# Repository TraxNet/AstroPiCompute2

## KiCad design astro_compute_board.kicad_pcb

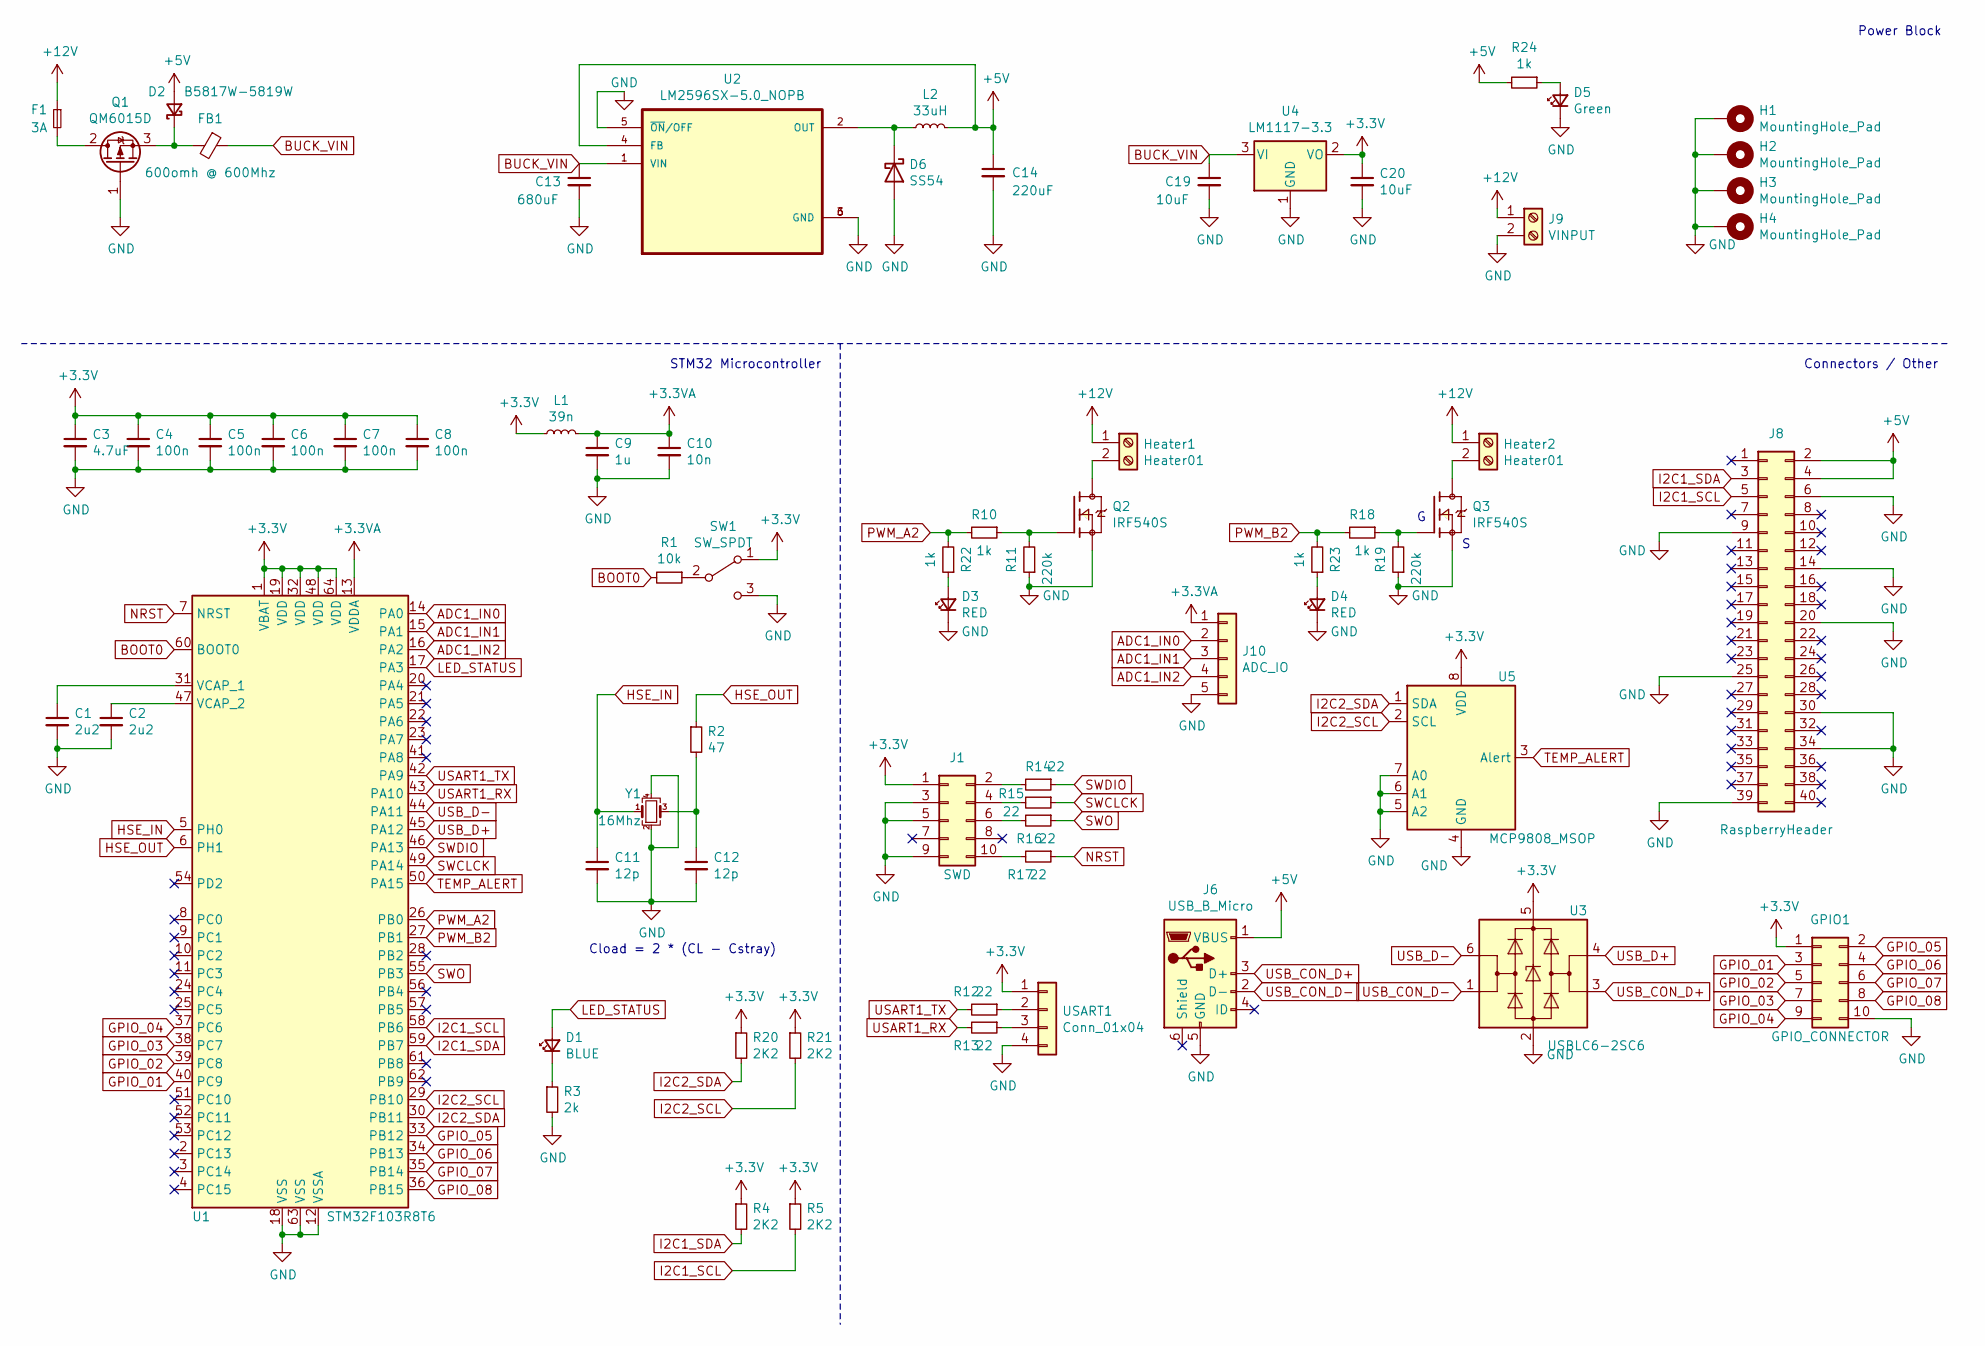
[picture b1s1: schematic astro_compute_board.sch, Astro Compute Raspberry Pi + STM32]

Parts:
C1, C2: 2u2; C_0603_1608Metric; LCSC Part # C23630
C3: 4.7uF; C_0402_1005Metric; LCSC Part # C23733
C4, C5, C6, C7, C8: 100n; C_0402_1005Metric; LCSC Part # C1525
C9: 1u; C_0402_1005Metric; LCSC Part # C52923
C10: 10n; C_0402_1005Metric; LCSC Part # C15195
C11, C12: 12p; C_0402_1005Metric; LCSC Part # C1547
C13: 680uF; CP_Radial_D8.0mm_P3.50mm; LCSC Part # C13585
C14: 220uF; CP_Radial_D6.3mm_P2.50mm; LCSC Part # C13585
C19, C20: 10uF; C_1206_3216Metric; LCSC Part # C13585
D1: BLUE; LED_0603_1608Metric; LCSC Part # C72041
D2: B5817W-5819W; D_SOD-123; LCSC Part # C8598
D3, D4: RED; LED_0603_1608Metric; LCSC Part # C2286
D5: Green; LED_0603_1608Metric; LCSC Part # C72043
D6: SS54; D_SMA; LCSC Part # C22452
F1: 3A; Fuse_1206_3216Metric
FB1: 600omh @ 600Mhz; L_0805_2012Metric; LCSC Part # C1017
GPIO1: GPIO_CONNECTOR; PinHeader_2x05_P1.27mm_Vertical_SMD
H1, H2, H3, H4: MountingHole_Pad; MountingHole_3.2mm_M3_Pad_Via
Heater1, Heater2: Heater01; TerminalBlock_bornier-2_P5.08mm
J1: SWD; PinHeader_2x05_P1.27mm_Vertical_SMD
J6: USB_B_Micro; USB_Micro-B_Molex-105017-0001; LCSC Part # C404969
J8: RaspberryHeader; PinHeader_2x20_P2.54mm_Vertical
J9: VINPUT; TerminalBlock_bornier-2_P5.08mm
J10: ADC_IO; Molex_PicoBlade_53048-0510_1x05_P1.25mm_Horizontal
L1: 39n; L_0402_1005Metric; LCSC Part # C26443
L2: 33uH; L_Radial_D7.5mm_P3.50mm_Fastron_07P
Q1: QM6015D; TO-252-2; LCSC Part # C238708
Q2, Q3: IRF540S; TO-263-2; PARTREV B; LCSC Part # C725068
R1: 10k; R_0402_1005Metric; LCSC Part # C25744
R2: 47; R_0402_1005Metric; LCSC Part # C25118
R3: 2k; R_0603_1608Metric; LCSC Part # C22975
R4, R5, R20, R21: 2K2; R_0805_2012Metric; LCSC Part # C17520
R10, R18, R22, R23, R24: 1k; R_0603_1608Metric; LCSC Part # C21190
R11, R19: 220k; R_0603_1608Metric; LCSC Part # C22961
R12, R13, R14, R15, R16, R17: 22; R_0402_1005Metric; LCSC Part # C25092
SW1: SW_SPDT; SW_SPDT_PCM12; LCSC Part # C431541
U1: STM32F103R8T6; LQFP-64_10x10mm_P0.5mm; LCSC Part # C46034
U2: LM2596SX-5.0_NOPB; NOPB; LCSC Part # C10002
U3: USBLC6-2SC6; SOT-23-6; LCSC Part # C7519
U4: LM1117-3.3; SOT-223; LCSC Part # C23984
U5: MCP9808_MSOP; MSOP-8_3x3mm_P0.65mm; LCSC Part # C129490
USART1: Conn_01x04; Molex_PicoBlade_53048-0410_1x04_P1.25mm_Horizontal
Y1: 16Mhz; Crystal_SMD_3225-4Pin_3.2x2.5mm; LCSC Part # C13738

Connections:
+3.3VA: C9.1, C10.1, J10.1, L1.2, U1.13 (VDDA)
+3V3: C3.1, C4.1, C5.1, C6.1, C7.1, C8.1, C20.1, GPIO1.1, J1.1, L1.1, R4.1, R5.1, R20.1, R21.1, SW1.1 (A), U1.1 (VBAT), U1.19 (VDD), U1.32 (VDD), U1.48 (VDD), U1.64 (VDD), U3.5 (VBUS), U4.2 (VO), U5.8 (VDD), USART1.1
+5V: C14.1, D2.2 (A), J6.1 (VBUS), J8.2, J8.4, L2.2, R24.2, U2.4 (FB)
+12V: F1.1, Heater1.1, Heater2.1, J9.1
ADC1_IN0: J10.2, U1.14 (PA0)
ADC1_IN1: J10.3, U1.15 (PA1)
ADC1_IN2: J10.4, U1.16 (PA2)
BOOT0: R1.2, U1.60 (BOOT0)
BUCK_VIN: C13.1, C19.1, FB1.1, U2.1 (VIN), U4.3 (VI)
GND: C1.2, C2.2, C3.2, C4.2, C5.2, C6.2, C7.2, C8.2, C9.2, C10.2, C11.2, C12.2, C13.2, C14.2, C19.2, C20.2, D3.1 (K), D4.1 (K), D5.1 (K), D6.2 (A), GPIO1.10, H1.1, H2.1, H3.1, H4.1, J1.3, J1.5, J1.9, J6.5 (GND), J8.6, J8.9, J8.14, J8.20, J8.25, J8.30, J8.34, J8.39, J9.2, J10.5, Q1.1 (G), Q2.3, Q3.3, R3.2, R11.1, R19.1, SW1.3 (C), U1.12 (VSSA), U1.18 (VSS), U1.63 (VSS), U2.3 (GND), U2.5 (~ON~/OFF), U2.6 (GND), U3.2 (GND), U4.1 (GND), U5.4 (GND), U5.5 (A2), U5.6 (A1), U5.7 (A0), USART1.4, Y1.2, Y1.4
GPIO_01: GPIO1.3, U1.40 (PC9)
GPIO_02: GPIO1.5, U1.39 (PC8)
GPIO_03: GPIO1.7, U1.38 (PC7)
GPIO_04: GPIO1.9, U1.37 (PC6)
GPIO_05: GPIO1.2, U1.33 (PB12)
GPIO_06: GPIO1.4, U1.34 (PB13)
GPIO_07: GPIO1.6, U1.35 (PB14)
GPIO_08: GPIO1.8, U1.36 (PB15)
HSE_IN: C11.1, U1.5 (PH0), Y1.1
HSE_OUT: R2.1, U1.6 (PH1)
I2C1_SCL: J8.5, R5.2, U1.58 (PB6)
I2C1_SDA: J8.3, R4.2, U1.59 (PB7)
I2C2_SCL: R21.2, U1.29 (PB10), U5.2 (SCL)
I2C2_SDA: R20.2, U1.30 (PB11), U5.1 (SDA)
LED_STATUS: D1.2 (A), U1.17 (PA3)
NRST: R17.1, U1.7 (NRST)
unnamed: C1.1, U1.31 (VCAP_1)
unnamed: C2.1, U1.47 (VCAP_2)
unnamed: C12.1, R2.2, Y1.3
unnamed: D1.1 (K), R3.1
unnamed: D2.1 (K), FB1.2, Q1.3 (S)
unnamed: D3.2 (A), R22.1
unnamed: D4.2 (A), R23.1
unnamed: D5.2 (A), R24.1
unnamed: D6.1 (K), L2.1, U2.2 (OUT)
unnamed: F1.2, Q1.2 (D)
unnamed: Heater1.2, Q2.2
unnamed: Heater2.2, Q3.2
unnamed: J1.2, R14.2
unnamed: J1.4, R15.2
unnamed: J1.6, R16.2
unnamed: J1.10, R17.2
unnamed: Q2.1, R10.1, R11.2
unnamed: Q3.1, R18.1, R19.2
unnamed: R1.1, SW1.2 (B)
unnamed: R12.1, USART1.2
unnamed: R13.1, USART1.3
PWM_A2: R10.2, R22.2, U1.26 (PB0)
PWM_B2: R18.2, R23.2, U1.27 (PB1)
SWCLCK: R15.1, U1.49 (PA14)
SWDIO: R14.1, U1.46 (PA13)
SWO: R16.1, U1.55 (PB3)
TEMP_ALERT: U1.50 (PA15), U5.3 (Alert)
USART1_RX: R13.2, U1.43 (PA10)
USART1_TX: R12.2, U1.42 (PA9)
USB_CON_D+: J6.3 (D+), U3.3 (I/O2)
USB_CON_D-: J6.2 (D-), U3.1 (I/O1)
USB_D+: U1.45 (PA12), U3.4 (I/O2)
USB_D-: U1.44 (PA11), U3.6 (I/O1)

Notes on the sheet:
Cload = 2 * (CL - Cstray)
STM32 Microcontroller
Power Block
Connectors / Other

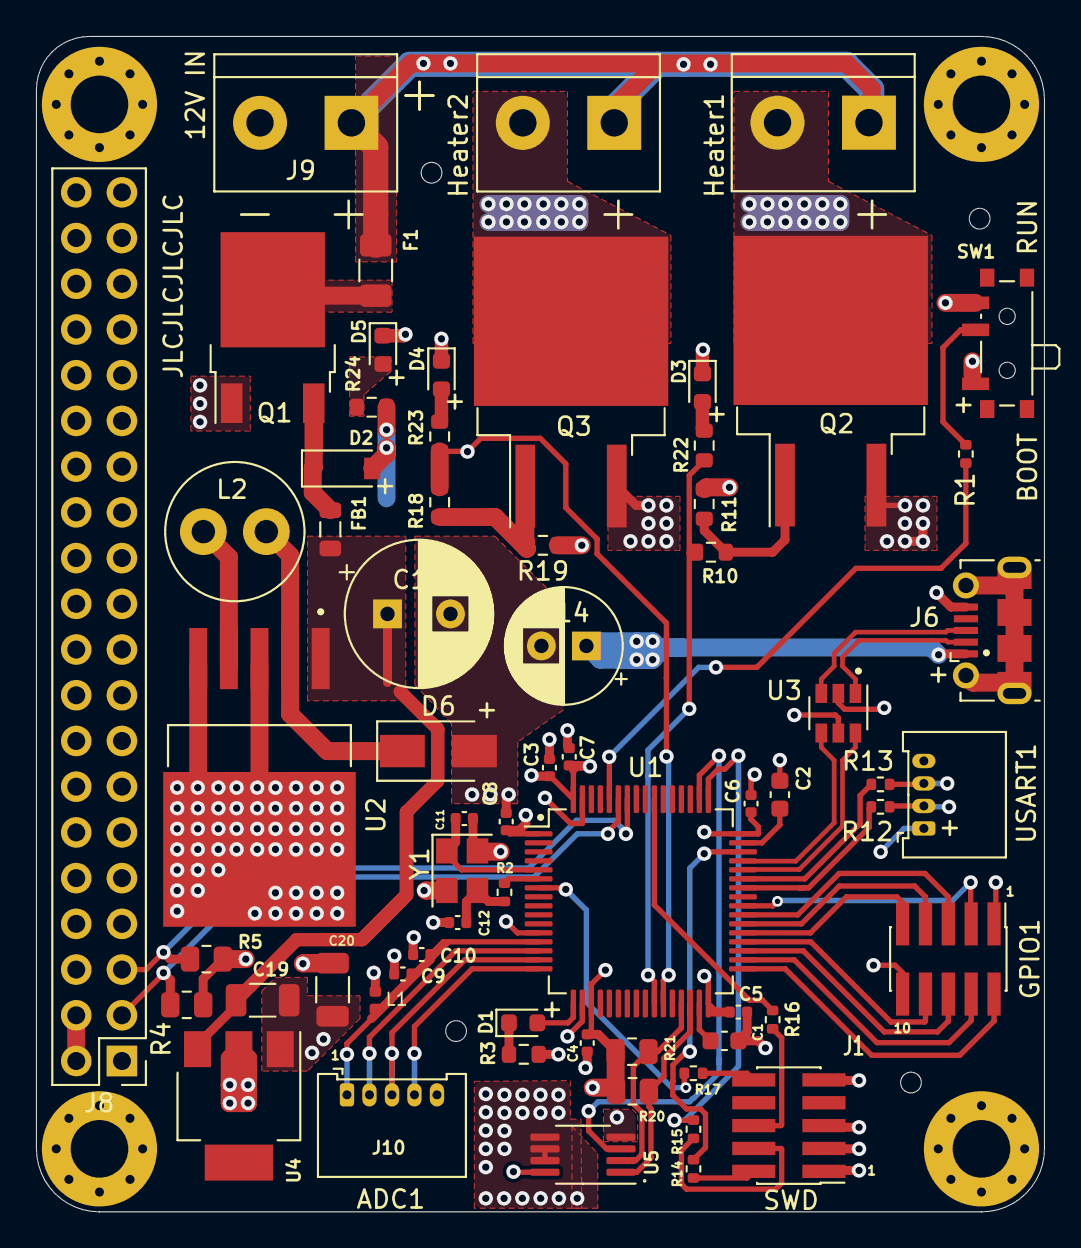
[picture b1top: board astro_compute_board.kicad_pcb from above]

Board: 4 copper layers, 56.0 x 65.3 mm, 69 parts (0 on the bottom side), 59 nets.

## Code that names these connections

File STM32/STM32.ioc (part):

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Mcu.Name=STM32F103R(8-B)Tx
Mcu.Package=LQFP64
Mcu.UserName=STM32F103R8Tx
PA0-WKUP.Signal=ADCx_IN0
PA1.Signal=ADCx_IN1
PA10.Signal=USART1_RX
PA11.Mode=Device
PA11.Signal=USB_DM
PA12.Mode=Device
PA12.Signal=USB_DP
PA13.Signal=SYS_JTMS-SWDIO
PA2.Signal=ADCx_IN2
PA9.Signal=USART1_TX
PB10.Signal=I2C2_SCL
PB11.Signal=I2C2_SDA
PB12.Signal=GPIO_Input
PB13.Signal=GPIO_Input
PB14.Signal=GPIO_Input
PB15.Signal=GPIO_Input
PC6.Signal=GPIO_Input
PC7.Signal=GPIO_Input
PC8.Signal=GPIO_Input
PC9.Signal=GPIO_Input
board=custom

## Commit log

2020-11-20 Initial Repo Commit
    All m ain components in schematic
2020-11-22 Extra files
2020-11-22 Board almost done. Major simplifications ahead
2020-11-24 JLCPCB Ready (but costly)
    Contains many extender parts that make PCB expensive.
2021-04-12 Rev2 - Out of Stock componets update (JLCPCB)
2021-04-13 Rev2.1 - Redesigned using Bulk Coverter and TH componets for easy testing
2021-04-17 Minor clean-ups
